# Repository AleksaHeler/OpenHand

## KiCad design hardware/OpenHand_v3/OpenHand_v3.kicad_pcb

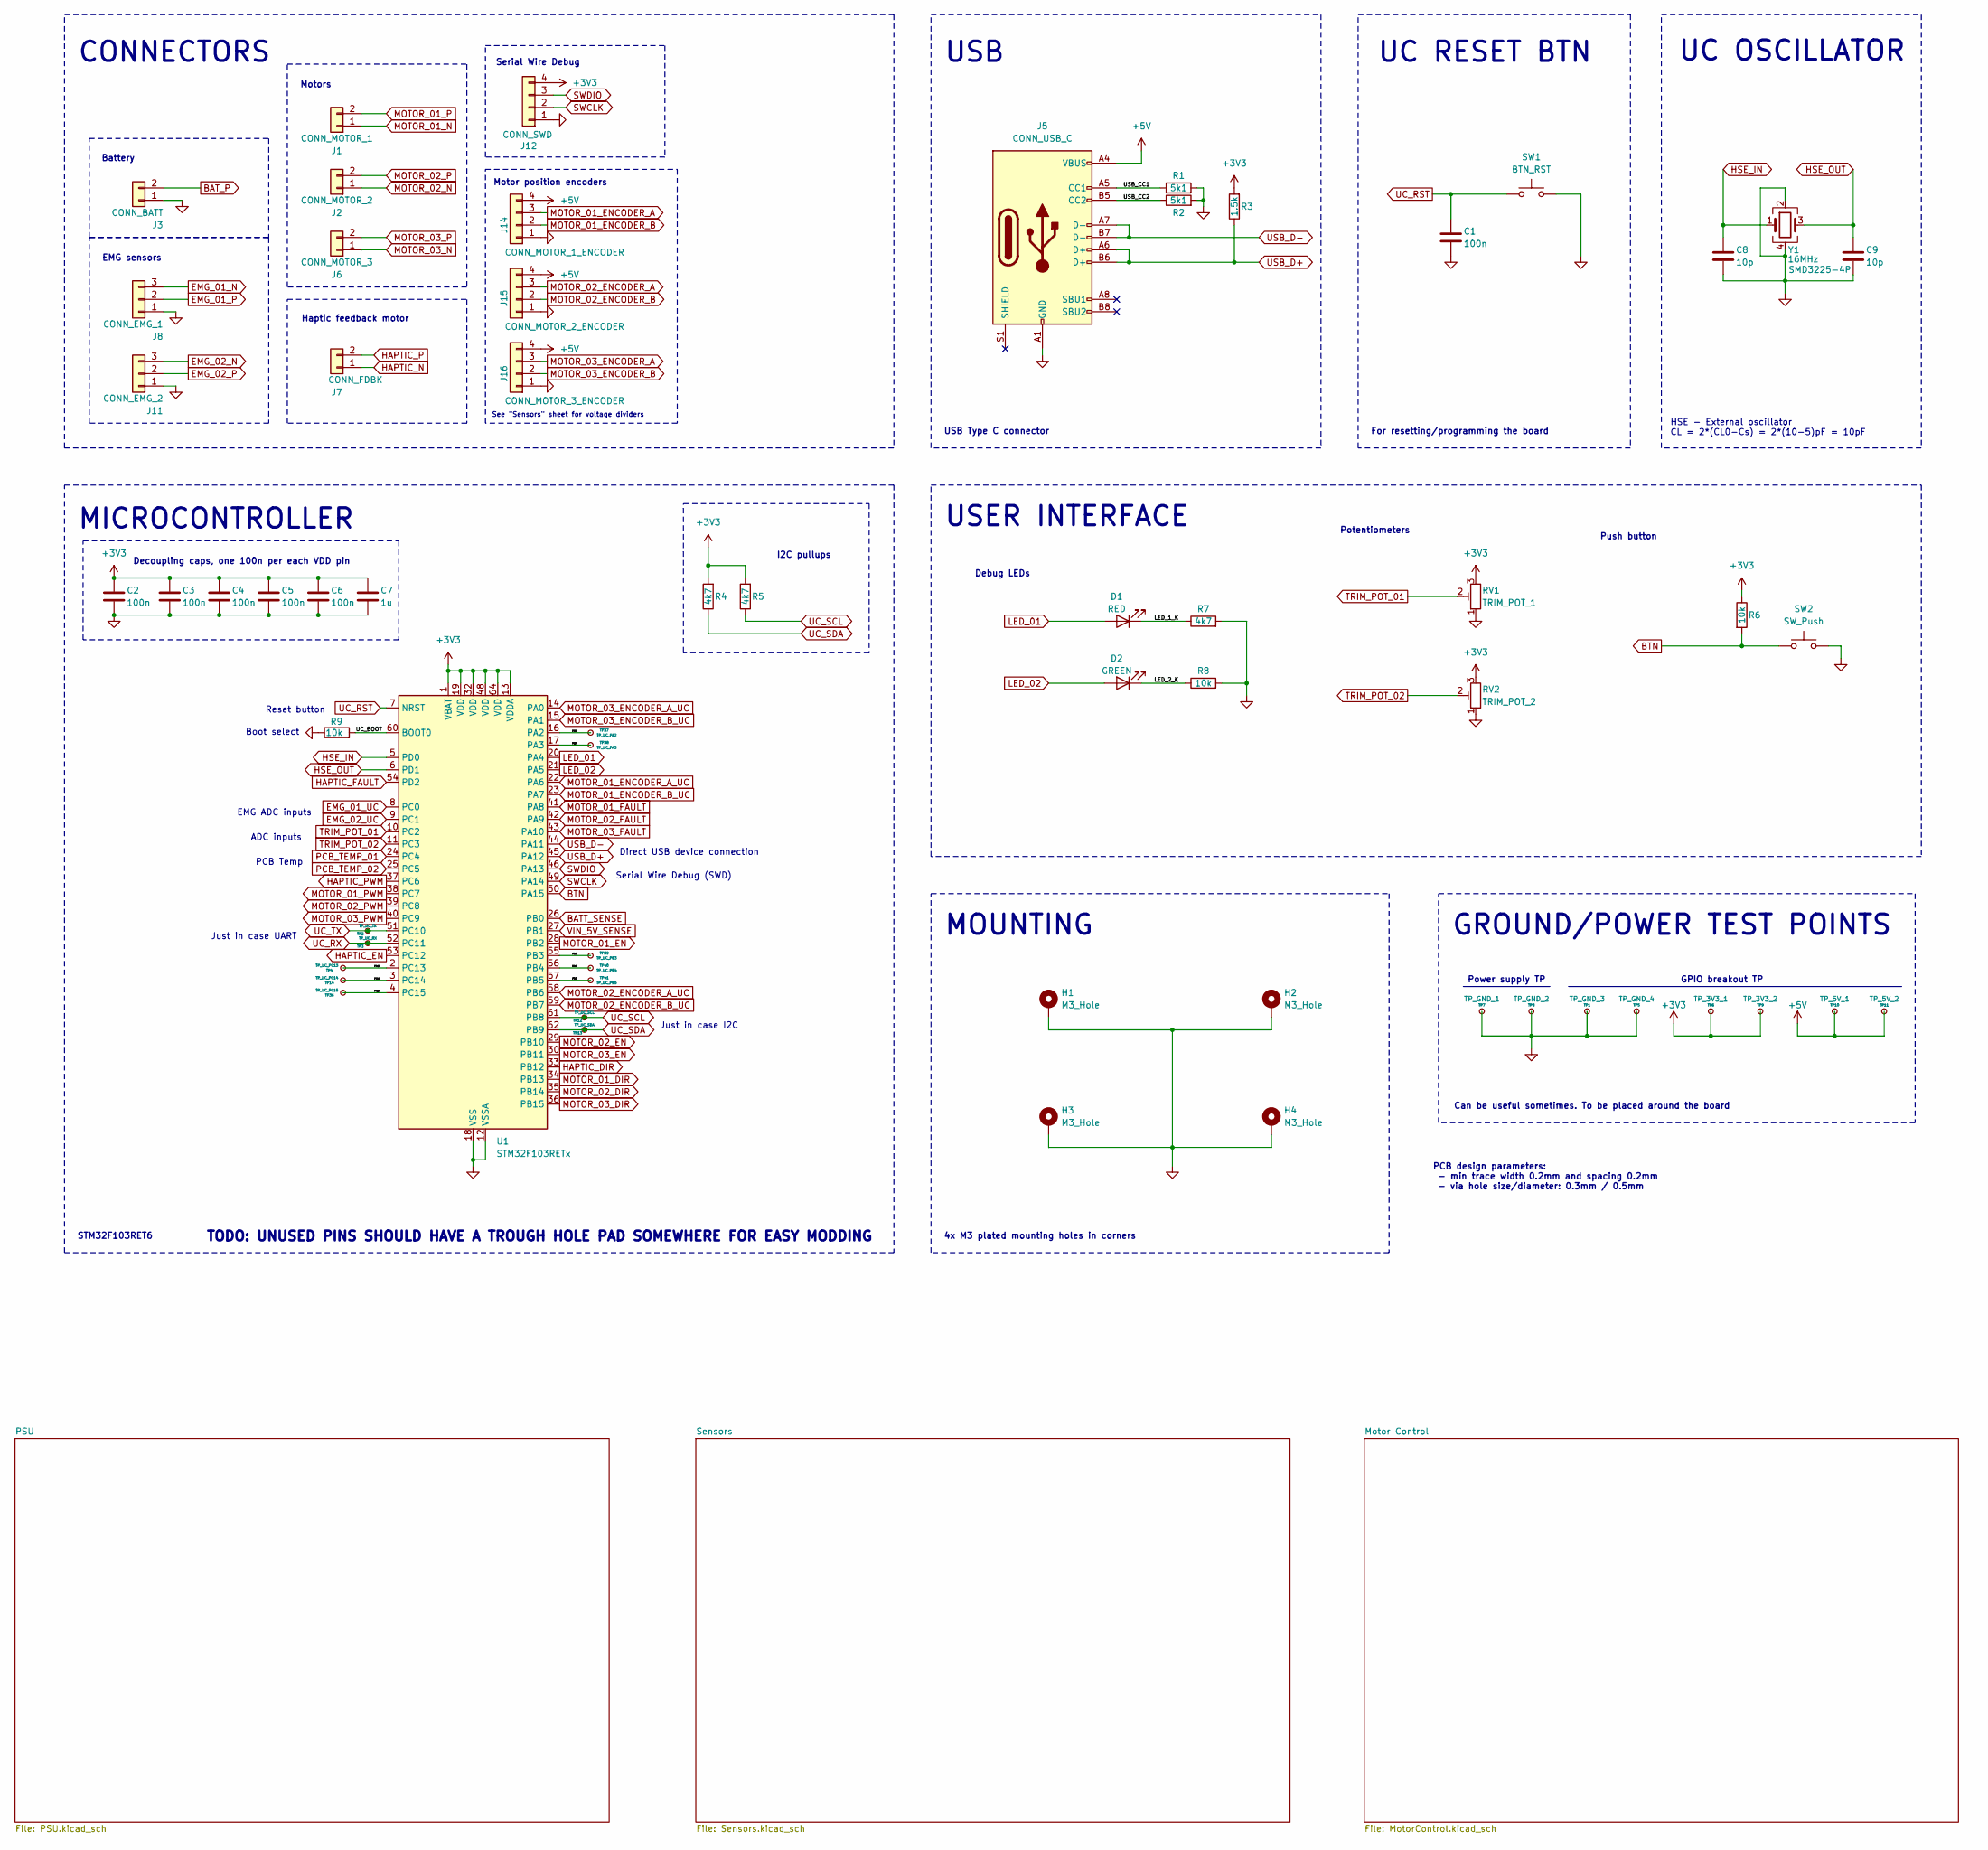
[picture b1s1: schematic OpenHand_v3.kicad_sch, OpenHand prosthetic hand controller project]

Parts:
C1, C2, C3, C4, C5, C6: 100n; C_0805_2012Metric
C7: 1u; C_0805_2012Metric
C8, C9: 10p; C_0805_2012Metric
D1: RED; LED_1210_3225Metric
D2: GREEN; LED_1210_3225Metric
H1, H2, H3, H4: M3_Hole; MountingHole_3.2mm_M3_Pad_Via
J1: CONN_MOTOR_1; JST_EH_S2B-EH_1x02_P2.50mm_Horizontal
J2: CONN_MOTOR_2; JST_EH_S2B-EH_1x02_P2.50mm_Horizontal
J3: CONN_BATT; JST_EH_S2B-EH_1x02_P2.50mm_Horizontal
J5: CONN_USB_C; USB_C_Receptacle_G-Switch_GT-USB-7010ASV
J6: CONN_MOTOR_3; JST_EH_S2B-EH_1x02_P2.50mm_Horizontal
J7: CONN_FDBK; JST_EH_S2B-EH_1x02_P2.50mm_Horizontal
J8: CONN_EMG_1; JST_XH_B3B-XH-A_1x03_P2.50mm_Vertical
J11: CONN_EMG_2; JST_XH_B3B-XH-A_1x03_P2.50mm_Vertical
J12: CONN_SWD; JST_XH_B4B-XH-A_1x04_P2.50mm_Vertical
J14: CONN_MOTOR_1_ENCODER; JST_XH_B4B-XH-A_1x04_P2.50mm_Vertical
J15: CONN_MOTOR_2_ENCODER; JST_XH_B4B-XH-A_1x04_P2.50mm_Vertical
J16: CONN_MOTOR_3_ENCODER; JST_XH_B4B-XH-A_1x04_P2.50mm_Vertical
R1, R2: 5k1; R_0805_2012Metric
R3: 1.5k; R_0805_2012Metric
R4, R5, R7: 4k7; R_0805_2012Metric
R6, R8, R9: 10k; R_0805_2012Metric
RV1: TRIM_POT_1; Potentiometer_Vishay_TS53YJ_Vertical
RV2: TRIM_POT_2; Potentiometer_Vishay_TS53YJ_Vertical
SW1: BTN_RST; SW_Tactile_SPST_NO_Straight_CK_PTS636Sx25SMTRLFS
SW2: SW_Push; SW_Tactile_SPST_NO_Straight_CK_PTS636Sx25SMTRLFS
TP1: TP_GND_3; TestPoint_THTPad_D1.5mm_Drill0.7mm
TP2: TP_UC_TX; TestPoint_THTPad_D1.5mm_Drill0.7mm
TP3: TP_UC_RX; TestPoint_THTPad_D1.5mm_Drill0.7mm
TP4: TP_UC_PC13; TestPoint_THTPad_D1.5mm_Drill0.7mm
TP5: TP_GND_4; TestPoint_THTPad_D1.5mm_Drill0.7mm
TP6: TP_3V3_1; TestPoint_THTPad_D1.5mm_Drill0.7mm
TP7: TP_GND_1; TestPoint_THTPad_D1.5mm_Drill0.7mm
TP8: TP_GND_2; TestPoint_THTPad_D1.5mm_Drill0.7mm
TP9: TP_3V3_2; TestPoint_THTPad_D1.5mm_Drill0.7mm
TP10: TP_5V_1; TestPoint_THTPad_D1.5mm_Drill0.7mm
TP11: TP_5V_2; TestPoint_THTPad_D1.5mm_Drill0.7mm
TP12: TP_UC_SCL; TestPoint_THTPad_D1.5mm_Drill0.7mm
TP13: TP_UC_SDA; TestPoint_THTPad_D1.5mm_Drill0.7mm
TP14: TP_UC_PC14; TestPoint_THTPad_D1.5mm_Drill0.7mm
TP36: TP_UC_PC15; TestPoint_THTPad_D1.5mm_Drill0.7mm
TP37: TP_UC_PA2; TestPoint_THTPad_D1.5mm_Drill0.7mm
TP38: TP_UC_PA3; TestPoint_THTPad_D1.5mm_Drill0.7mm
TP39: TP_UC_PB3; TestPoint_THTPad_D1.5mm_Drill0.7mm
TP40: TP_UC_PB4; TestPoint_THTPad_D1.5mm_Drill0.7mm
TP41: TP_UC_PB5; TestPoint_THTPad_D1.5mm_Drill0.7mm
U1: STM32F103RETx; LQFP-64_10x10mm_P0.5mm
Y1: 16MHz; Crystal_SMD_3225-4Pin_3.2x2.5mm

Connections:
+3V3: C2.1, C3.1, C4.1, C5.1, C6.1, C7.1, J12.4, R3.2, R4.2, R5.2, R6.1, RV1.3, RV2.3, TP6.1, TP9.1, U1.1 (VBAT), U1.13 (VDDA), U1.19 (VDD), U1.32 (VDD), U1.48 (VDD), U1.64 (VDD); also elsewhere on the board
+5V: J5.A4 (VBUS), J5.A9 (VBUS), J5.B4 (VBUS), J5.B9 (VBUS), J14.4, J15.4, J16.4, TP10.1, TP11.1; also elsewhere on the board
/LED_1_K: D1.1 (K), R7.1
/LED_2_K: D2.1 (K), R8.1
/PA2: TP37.1, U1.16 (PA2)
/PA3: TP38.1, U1.17 (PA3)
/PB3: TP39.1, U1.55 (PB3)
/PB4: TP40.1, U1.56 (PB4)
/PB5: TP41.1, U1.57 (PB5)
/PC13: TP4.1, U1.2 (PC13)
/PC14: TP14.1, U1.3 (PC14)
/PC15: TP36.1, U1.4 (PC15)
/UC_BOOT: R9.2, U1.60 (BOOT0)
/USB_CC1: J5.A5 (CC1), R1.1
/USB_CC2: J5.B5 (CC2), R2.1
BATT_SENSE: U1.26 (PB0); also elsewhere on the board
BAT_P: J3.2; also elsewhere on the board
BTN: R6.2, SW2.1, U1.50 (PA15)
EMG_01_N: J8.3; also elsewhere on the board
EMG_01_P: J8.2; also elsewhere on the board
EMG_01_UC: U1.8 (PC0); also elsewhere on the board
EMG_02_N: J11.3; also elsewhere on the board
EMG_02_P: J11.2; also elsewhere on the board
EMG_02_UC: U1.9 (PC1); also elsewhere on the board
GND: C1.2, C2.2, C3.2, C4.2, C5.2, C6.2, C7.2, C8.2, C9.2, H1.1, H2.1, H3.1, H4.1, J3.1, J5.A1 (GND), J5.A12 (GND), J5.B1 (GND), J5.B12 (GND), J8.1, J11.1, J12.1, J14.1, J15.1, J16.1, R1.2, R2.2, R7.2, R8.2, R9.1, RV1.1, RV2.1, SW1.2, SW2.2, TP1.1, TP5.1, TP7.1, TP8.1, U1.12 (VSSA), U1.18 (VSS), U1.31 (VSS), U1.47 (VSS), U1.63 (VSS), Y1.2, Y1.4; also elsewhere on the board
HAPTIC_DIR: U1.33 (PB12); also elsewhere on the board
HAPTIC_EN: U1.53 (PC12); also elsewhere on the board
HAPTIC_FAULT: U1.54 (PD2); also elsewhere on the board
HAPTIC_N: J7.1; also elsewhere on the board
HAPTIC_P: J7.2; also elsewhere on the board
HAPTIC_PWM: U1.37 (PC6); also elsewhere on the board
HSE_IN: C8.1, U1.5 (PD0), Y1.1
HSE_OUT: C9.1, U1.6 (PD1), Y1.3
LED_01: D1.2 (A), U1.20 (PA4)
LED_02: D2.2 (A), U1.21 (PA5)
MOTOR_01_DIR: U1.34 (PB13); also elsewhere on the board
MOTOR_01_EN: U1.28 (PB2); also elsewhere on the board
MOTOR_01_ENCODER_A: J14.3; also elsewhere on the board
MOTOR_01_ENCODER_A_UC: U1.22 (PA6); also elsewhere on the board
MOTOR_01_ENCODER_B: J14.2; also elsewhere on the board
MOTOR_01_ENCODER_B_UC: U1.23 (PA7); also elsewhere on the board
MOTOR_01_FAULT: U1.41 (PA8); also elsewhere on the board
MOTOR_01_N: J1.1; also elsewhere on the board
MOTOR_01_P: J1.2; also elsewhere on the board
MOTOR_01_PWM: U1.38 (PC7); also elsewhere on the board
MOTOR_02_DIR: U1.35 (PB14); also elsewhere on the board
MOTOR_02_EN: U1.29 (PB10); also elsewhere on the board
MOTOR_02_ENCODER_A: J15.3; also elsewhere on the board
MOTOR_02_ENCODER_A_UC: U1.58 (PB6); also elsewhere on the board
MOTOR_02_ENCODER_B: J15.2; also elsewhere on the board
MOTOR_02_ENCODER_B_UC: U1.59 (PB7); also elsewhere on the board
MOTOR_02_FAULT: U1.42 (PA9); also elsewhere on the board
MOTOR_02_N: J2.1; also elsewhere on the board
MOTOR_02_P: J2.2; also elsewhere on the board
MOTOR_02_PWM: U1.39 (PC8); also elsewhere on the board
MOTOR_03_DIR: U1.36 (PB15); also elsewhere on the board
MOTOR_03_EN: U1.30 (PB11); also elsewhere on the board
MOTOR_03_ENCODER_A: J16.3; also elsewhere on the board
MOTOR_03_ENCODER_A_UC: U1.14 (PA0); also elsewhere on the board
MOTOR_03_ENCODER_B: J16.2; also elsewhere on the board
MOTOR_03_ENCODER_B_UC: U1.15 (PA1); also elsewhere on the board
MOTOR_03_FAULT: U1.43 (PA10); also elsewhere on the board
MOTOR_03_N: J6.1; also elsewhere on the board
MOTOR_03_P: J6.2; also elsewhere on the board
MOTOR_03_PWM: U1.40 (PC9); also elsewhere on the board
PCB_TEMP_01: U1.24 (PC4); also elsewhere on the board
PCB_TEMP_02: U1.25 (PC5); also elsewhere on the board
SWCLK: J12.2, U1.49 (PA14)
SWDIO: J12.3, U1.46 (PA13)
TRIM_POT_01: RV1.2, U1.10 (PC2)
TRIM_POT_02: RV2.2, U1.11 (PC3)
UC_RST: C1.1, SW1.1, U1.7 (NRST)
UC_RX: TP3.1, U1.52 (PC11)
UC_SCL: R5.1, TP12.1, U1.61 (PB8)
UC_SDA: R4.1, TP13.1, U1.62 (PB9)
UC_TX: TP2.1, U1.51 (PC10)
USB_D+: J5.A6 (D+), J5.B6 (D+), R3.1, U1.45 (PA12)
USB_D-: J5.A7 (D-), J5.B7 (D-), U1.44 (PA11)
VIN_5V_SENSE: U1.27 (PB1); also elsewhere on the board

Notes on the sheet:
I2C pullups
Debug LEDs
UC RESET BTN
Potentiometers
ADC inputs
Serial Wire Debug (SWD)
MICROCONTROLLER
Battery
PCB Temp
Haptic feedback motor
Reset button
Just in case I2C
USB
Push button
4x M3 plated mounting holes in corners
TODO: UNUSED PINS SHOULD HAVE A TROUGH HOLE PAD SOMEWHERE FOR EASY MODDING
Power supply TP
Motors
MOUNTING
CONNECTORS
PCB design parameters: - min trace width 0.2mm and spacing 0.2mm - via hole size/diameter: 0.3mm / 0.5mm
EMG ADC inputs
For resetting/programming the board
Can be useful sometimes. To be placed around the board
USB Type C connector
Decoupling caps, one 100n per each VDD pin
USER INTERFACE
STM32F103RET6
GROUND/POWER TEST POINTS
Boot select
GPIO breakout TP
EMG sensors
Direct USB device connection
HSE - External oscillator CL = 2*(CL0-Cs) = 2*(10-5)pF = 10pF
See "Sensors" sheet for voltage dividers
UC OSCILLATOR
Just in case UART
Serial Wire Debug
Motor position encoders

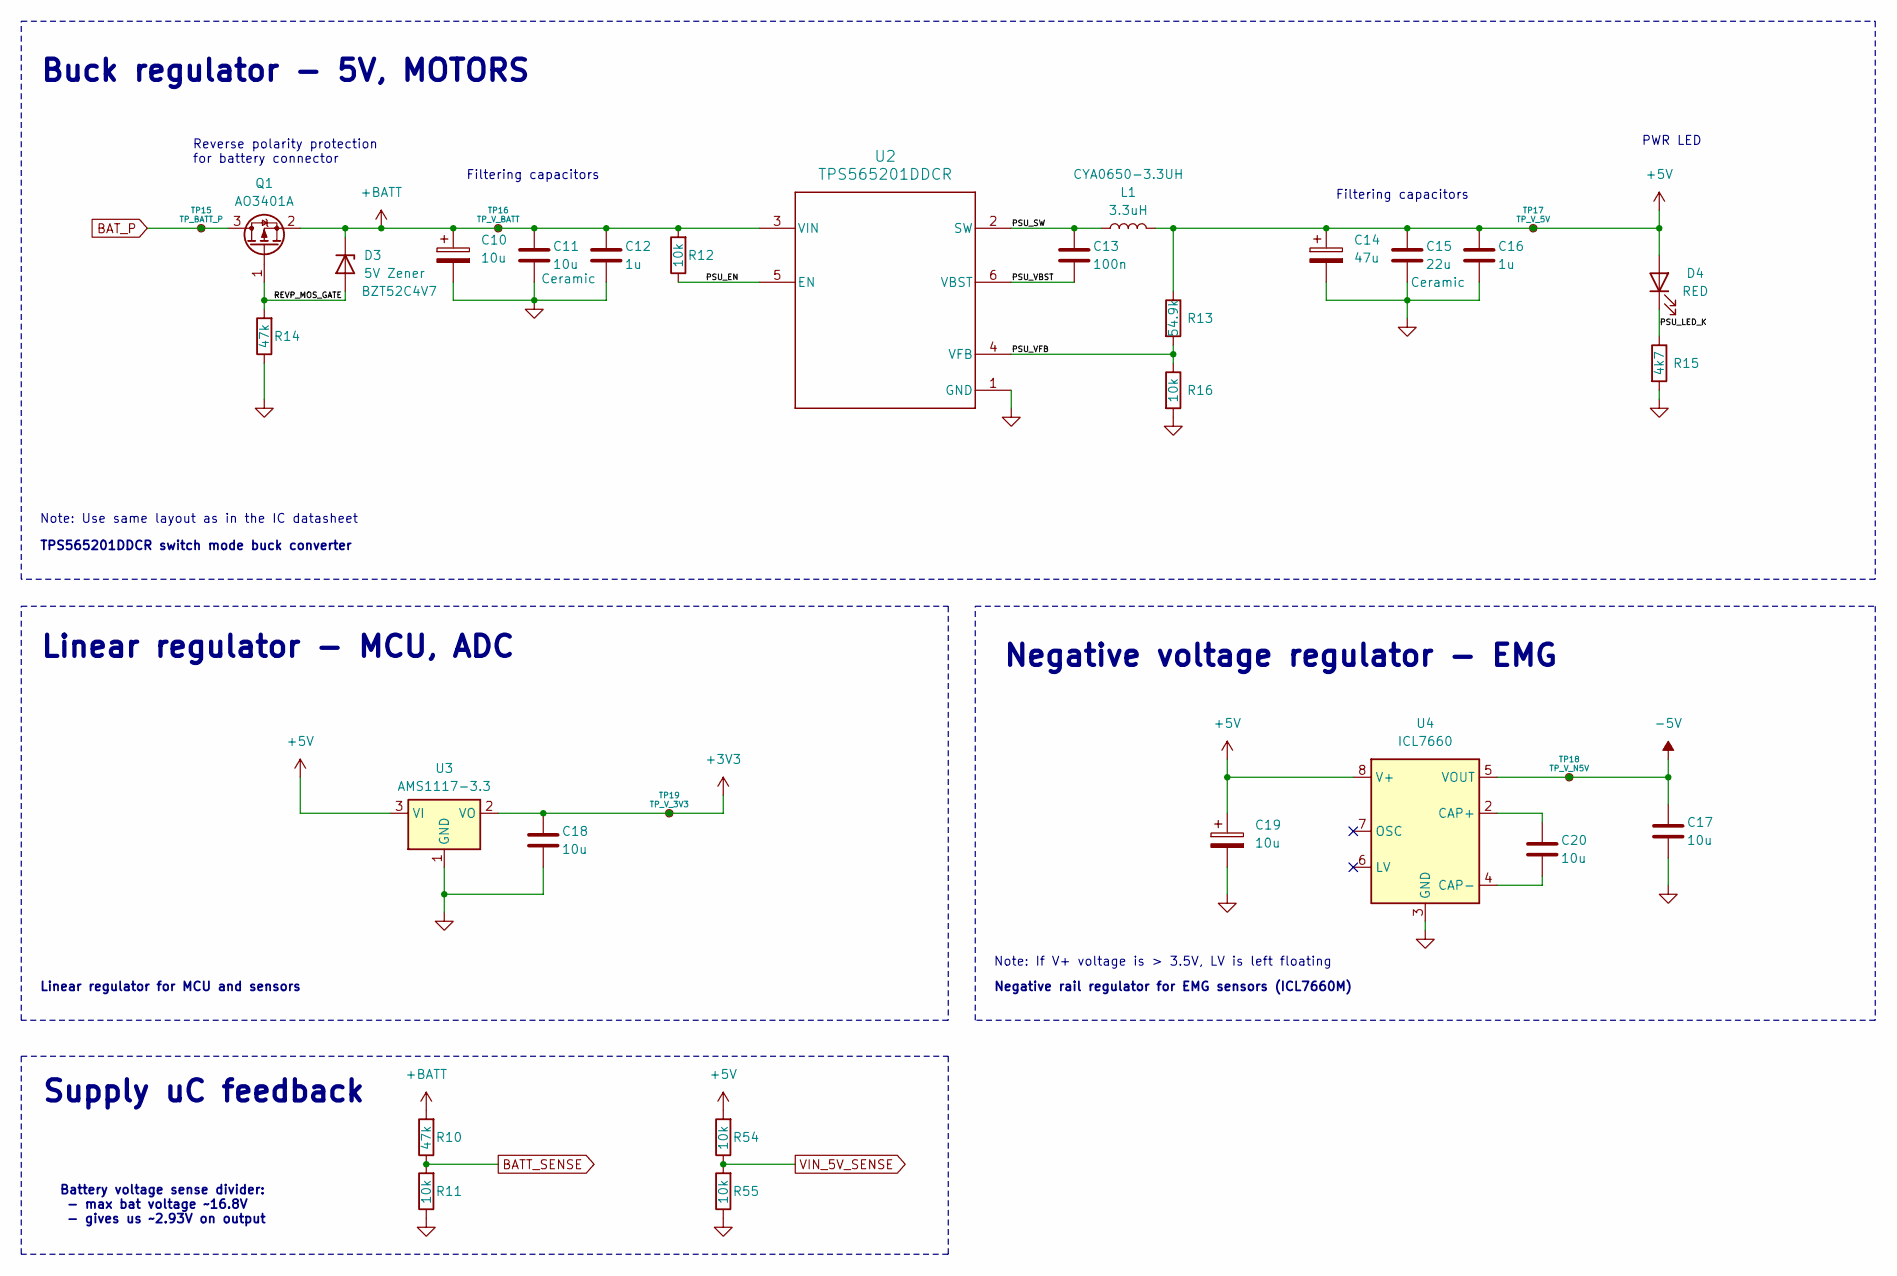
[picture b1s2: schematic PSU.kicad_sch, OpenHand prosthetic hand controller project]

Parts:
C10, C19: 10u; CP_Elec_4x5.4
C11, C17, C18, C20: 10u; C_0805_2012Metric
C12, C16: 1u; C_0805_2012Metric
C13: 100n; C_0805_2012Metric
C14: 47u; CP_Elec_6.3x5.4
C15: 22u; C_0805_2012Metric
D3: 5V Zener; D_SOD-123; Part Number BZT52C4V7
D4: RED; LED_1210_3225Metric
L1: 3.3uH; L_Bourns_SRP7028A_7.3x6.6mm; Part Number CYA0650-3.3UH
Q1: AO3401A; SOT-23
R10, R14: 47k; R_0805_2012Metric
R11, R12, R16, R54, R55: 10k; R_0805_2012Metric
R13: 54.9k; R_0805_2012Metric
R15: 4k7; R_0805_2012Metric
TP15: TP_BATT_P; TestPoint_Pad_D1.0mm
TP16: TP_V_BATT; TestPoint_Pad_D1.0mm
TP17: TP_V_5V; TestPoint_THTPad_D1.5mm_Drill0.7mm
TP18: TP_V_N5V; TestPoint_THTPad_D1.5mm_Drill0.7mm
TP19: TP_V_3V3; TestPoint_THTPad_D1.5mm_Drill0.7mm
U2: TPS565201DDCR; TPS565201DDCR_L
U3: AMS1117-3.3; SOT-223-3_TabPin2
U4: ICL7660; SOP-8_3.9x4.9mm_P1.27mm

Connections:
+3V3: C18.1, TP19.1, U3.2 (VO); also elsewhere on the board
+5V: C14.1, C15.1, C16.1, C19.1, D4.2 (A), L1.2, R13.1, R54.2, TP17.1, U3.3 (VI), U4.8 (V+); also elsewhere on the board
+BATT: C10.1, C11.1, C12.1, D3.1 (K), Q1.2 (S), R10.2, R12.2, TP16.1, U2.3 (VIN)
-5V: C17.1, TP18.1, U4.5 (VOUT); also elsewhere on the board
/PSU/PSU_EN: R12.1, U2.5 (EN)
/PSU/PSU_LED_K: D4.1 (K), R15.1
/PSU/PSU_SW: C13.1, L1.1, U2.2 (SW)
/PSU/PSU_VBST: C13.2, U2.6 (VBST)
/PSU/PSU_VFB: R13.2, R16.1, U2.4 (VFB)
/PSU/REVP_MOS_GATE: D3.2 (A), Q1.1 (G), R14.2
BATT_SENSE: R10.1, R11.2; also elsewhere on the board
BAT_P: Q1.3 (D), TP15.1; also elsewhere on the board
GND: C10.2, C11.2, C12.2, C14.2, C15.2, C16.2, C17.2, C18.2, C19.2, R11.1, R14.1, R15.2, R16.2, R55.1, U2.1 (GND), U3.1 (GND), U4.3 (GND); also elsewhere on the board
unnamed: C20.1, U4.2 (CAP+)
unnamed: C20.2, U4.4 (CAP-)
VIN_5V_SENSE: R54.1, R55.2; also elsewhere on the board

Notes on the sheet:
Linear regulator - MCU, ADC
Note: Use same layout as in the IC datasheet
Filtering capacitors
Supply uC feedback
PWR LED
Note: If V+ voltage is > 3.5V, LV is left floating
Negative voltage regulator - EMG
Buck regulator - 5V, MOTORS
TPS565201DDCR switch mode buck converter
Battery voltage sense divider: - max bat voltage ~16.8V - gives us ~2.93V on output
Negative rail regulator for EMG sensors (ICL7660M)
Linear regulator for MCU and sensors
Reverse polarity protection for battery connector

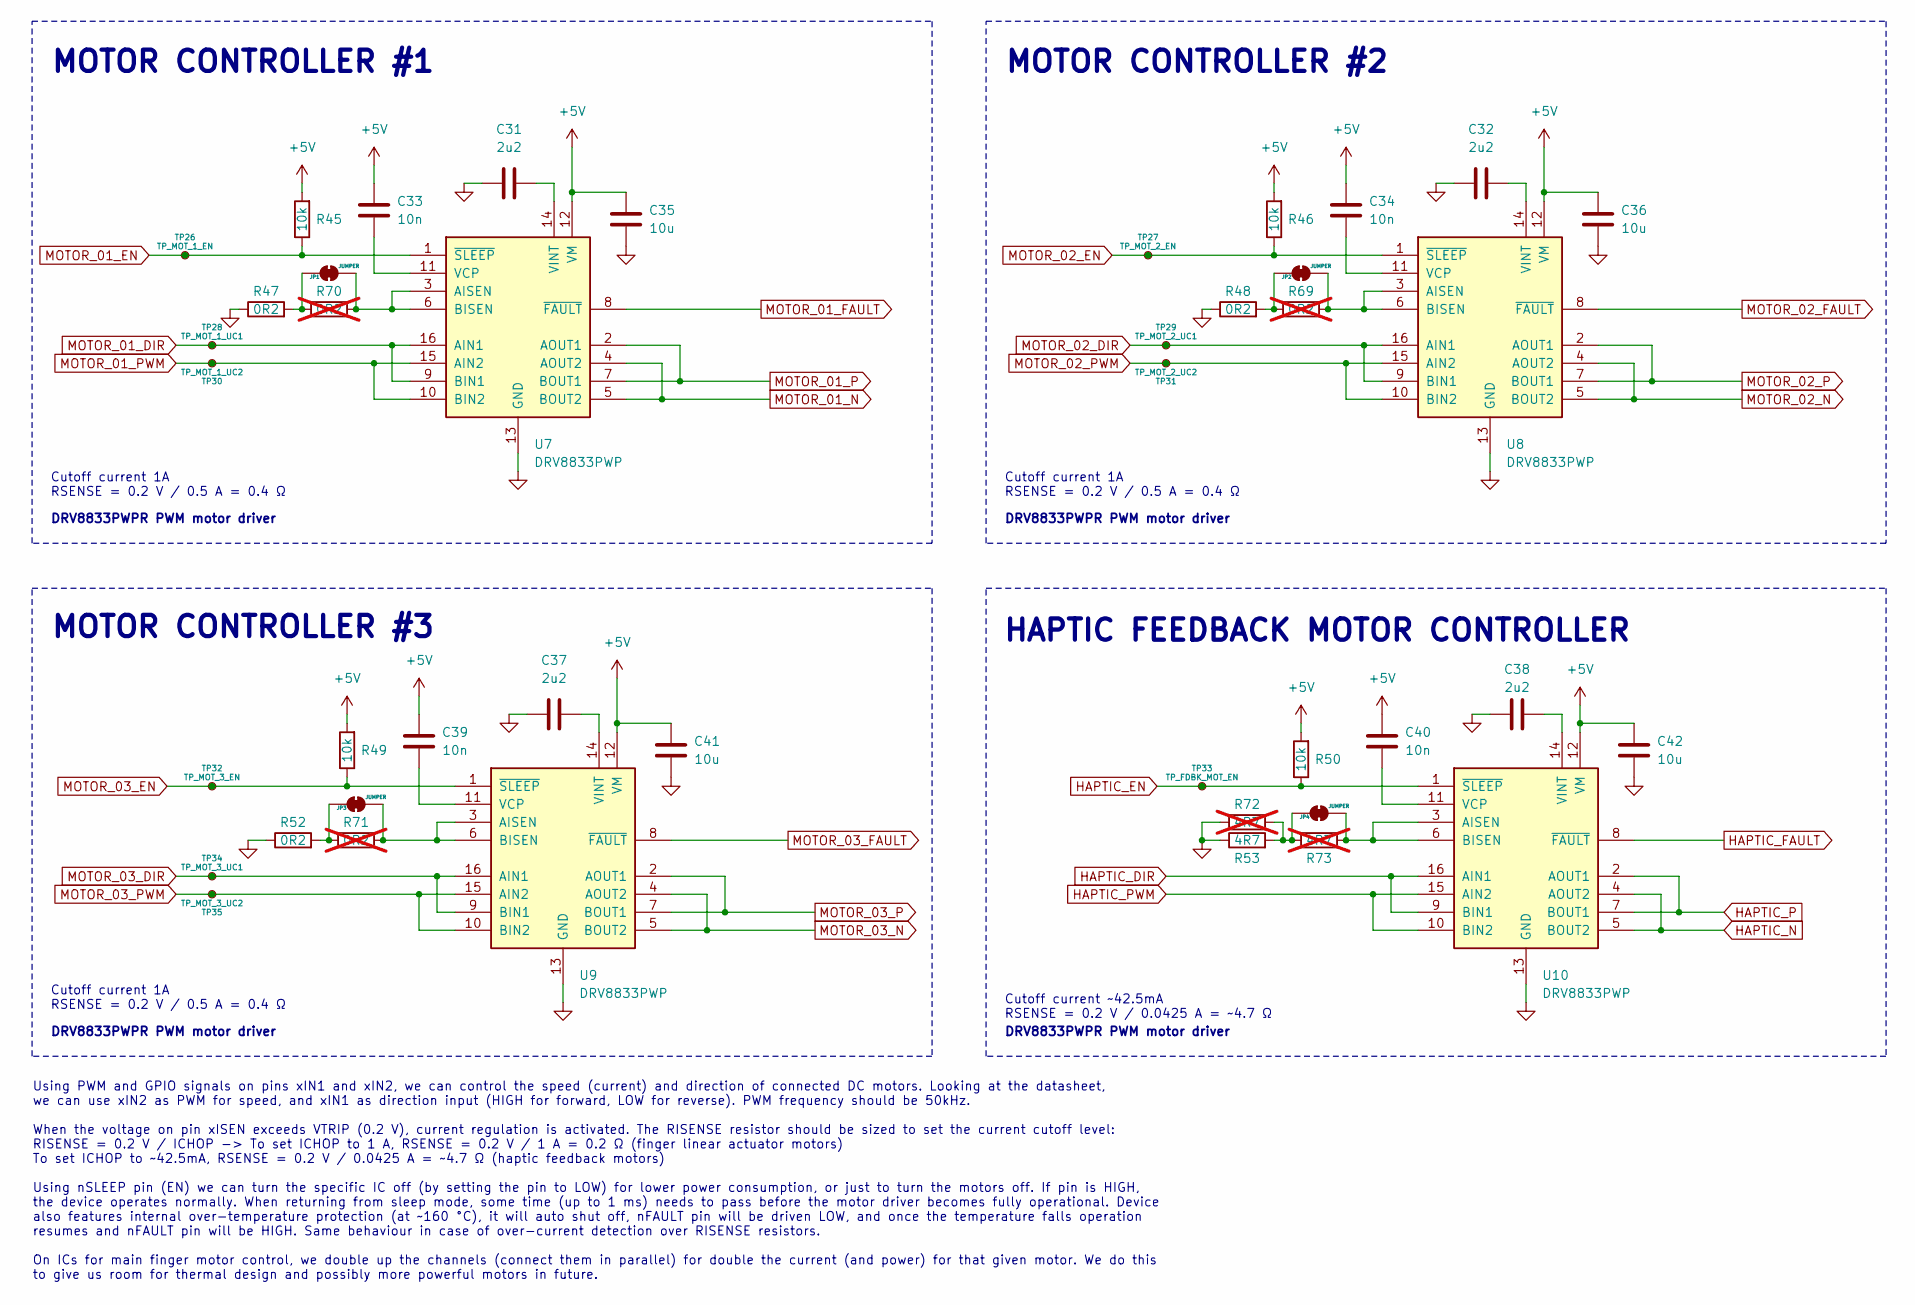
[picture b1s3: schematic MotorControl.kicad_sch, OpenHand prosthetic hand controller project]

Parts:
C31, C32, C37, C38: 2u2; C_0805_2012Metric
C33, C34, C39, C40: 10n; C_0805_2012Metric
C35, C36, C41, C42: 10u; C_0805_2012Metric
JP1, JP2, JP3, JP4: JUMPER; SolderJumper-2_P1.3mm_Bridged_RoundedPad1.0x1.5mm
R45, R46, R49, R50: 10k; R_0805_2012Metric
R47, R48, R52: 0R2; R_1206_3216Metric
R53: 4R7; R_1206_3216Metric
R69, R70, R71: 0R2; R_1206_3216Metric; not fitted
R72, R73: 4R7; R_1206_3216Metric; not fitted
TP26: TP_MOT_1_EN; TestPoint_Pad_D1.0mm
TP27: TP_MOT_2_EN; TestPoint_Pad_D1.0mm
TP28: TP_MOT_1_UC1; TestPoint_Pad_D1.0mm
TP29: TP_MOT_2_UC1; TestPoint_Pad_D1.0mm
TP30: TP_MOT_1_UC2; TestPoint_Pad_D1.0mm
TP31: TP_MOT_2_UC2; TestPoint_Pad_D1.0mm
TP32: TP_MOT_3_EN; TestPoint_Pad_D1.0mm
TP33: TP_FDBK_MOT_EN; TestPoint_Pad_D1.0mm
TP34: TP_MOT_3_UC1; TestPoint_Pad_D1.0mm
TP35: TP_MOT_3_UC2; TestPoint_Pad_D1.0mm
U7, U8, U9, U10: DRV8833PWP; HTSSOP-16-1EP_4.4x5mm_P0.65mm_EP3.4x5mm_Mask2.46x2.31mm_The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

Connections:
+5V: C33.1, C34.1, C35.1, C36.1, C39.1, C40.1, C41.1, C42.1, R45.2, R46.2, R49.2, R50.2, U7.12 (VM), U8.12 (VM), U9.12 (VM), U10.12 (VM); also elsewhere on the board
GND: C31.1, C32.1, C35.2, C36.2, C37.1, C38.1, C41.2, C42.2, R47.1, R48.1, R52.1, R53.1, R72.2, U7.13 (GND), U7.17 (GND), U8.13 (GND), U8.17 (GND), U9.13 (GND), U9.17 (GND), U10.13 (GND), U10.17 (GND); also elsewhere on the board
HAPTIC_DIR: U10.9 (BIN1), U10.16 (AIN1); also elsewhere on the board
HAPTIC_EN: R50.1, TP33.1, U10.1 (~SLEEP); also elsewhere on the board
HAPTIC_FAULT: U10.8 (~FAULT); also elsewhere on the board
HAPTIC_N: U10.4 (AOUT2), U10.5 (BOUT2); also elsewhere on the board
HAPTIC_P: U10.2 (AOUT1), U10.7 (BOUT1); also elsewhere on the board
HAPTIC_PWM: U10.10 (BIN2), U10.15 (AIN2); also elsewhere on the board
MOTOR_01_DIR: TP28.1, U7.9 (BIN1), U7.16 (AIN1); also elsewhere on the board
MOTOR_01_EN: R45.1, TP26.1, U7.1 (~SLEEP); also elsewhere on the board
MOTOR_01_FAULT: U7.8 (~FAULT); also elsewhere on the board
MOTOR_01_N: U7.4 (AOUT2), U7.5 (BOUT2); also elsewhere on the board
MOTOR_01_P: U7.2 (AOUT1), U7.7 (BOUT1); also elsewhere on the board
MOTOR_01_PWM: TP30.1, U7.10 (BIN2), U7.15 (AIN2); also elsewhere on the board
MOTOR_02_DIR: TP29.1, U8.9 (BIN1), U8.16 (AIN1); also elsewhere on the board
MOTOR_02_EN: R46.1, TP27.1, U8.1 (~SLEEP); also elsewhere on the board
MOTOR_02_FAULT: U8.8 (~FAULT); also elsewhere on the board
MOTOR_02_N: U8.4 (AOUT2), U8.5 (BOUT2); also elsewhere on the board
MOTOR_02_P: U8.2 (AOUT1), U8.7 (BOUT1); also elsewhere on the board
MOTOR_02_PWM: TP31.1, U8.10 (BIN2), U8.15 (AIN2); also elsewhere on the board
MOTOR_03_DIR: TP34.1, U9.9 (BIN1), U9.16 (AIN1); also elsewhere on the board
MOTOR_03_EN: R49.1, TP32.1, U9.1 (~SLEEP); also elsewhere on the board
MOTOR_03_FAULT: U9.8 (~FAULT); also elsewhere on the board
MOTOR_03_N: U9.4 (AOUT2), U9.5 (BOUT2); also elsewhere on the board
MOTOR_03_P: U9.2 (AOUT1), U9.7 (BOUT1); also elsewhere on the board
MOTOR_03_PWM: TP35.1, U9.10 (BIN2), U9.15 (AIN2); also elsewhere on the board
unnamed: JP1.1 (A), R47.2, R70.1
unnamed: JP1.2 (B), R70.2, U7.3 (AISEN), U7.6 (BISEN)
unnamed: JP2.1 (A), R48.2, R69.1
unnamed: JP2.2 (B), R69.2, U8.3 (AISEN), U8.6 (BISEN)
unnamed: JP3.1 (A), R52.2, R71.1
unnamed: JP3.2 (B), R71.2, U9.3 (AISEN), U9.6 (BISEN)
unnamed: JP4.1 (A), R53.2, R72.1, R73.1
unnamed: JP4.2 (B), R73.2, U10.3 (AISEN), U10.6 (BISEN)
unnamed: C33.2, U7.11 (VCP)
unnamed: C31.2, U7.14 (VINT)
unnamed: C34.2, U8.11 (VCP)
unnamed: C32.2, U8.14 (VINT)
unnamed: C39.2, U9.11 (VCP)
unnamed: C37.2, U9.14 (VINT)
unnamed: C40.2, U10.11 (VCP)
unnamed: C38.2, U10.14 (VINT)

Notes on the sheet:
Cutoff current 1A RSENSE = 0.2 V / 0.5 A = 0.4 Ω
MOTOR CONTROLLER #1
DRV8833PWPR PWM motor driver
HAPTIC FEEDBACK MOTOR CONTROLLER
Using PWM and GPIO signals on pins xIN1 and xIN2, we can control the speed (current) and direction of connected DC motors. Looking at the datasheet, we can use xIN2 as PWM for speed, and xIN1 as direction input (HIGH for forward, LOW for reverse). PWM frequency should be 50kHz. When the voltage on 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
MOTOR CONTROLLER #3
MOTOR CONTROLLER #2
Cutoff current ~42.5mA RSENSE = 0.2 V / 0.0425 A = ~4.7 Ω
Cutoff current 1A RSENSE = 0.2 V / 0.5 A = 0.4 Ω

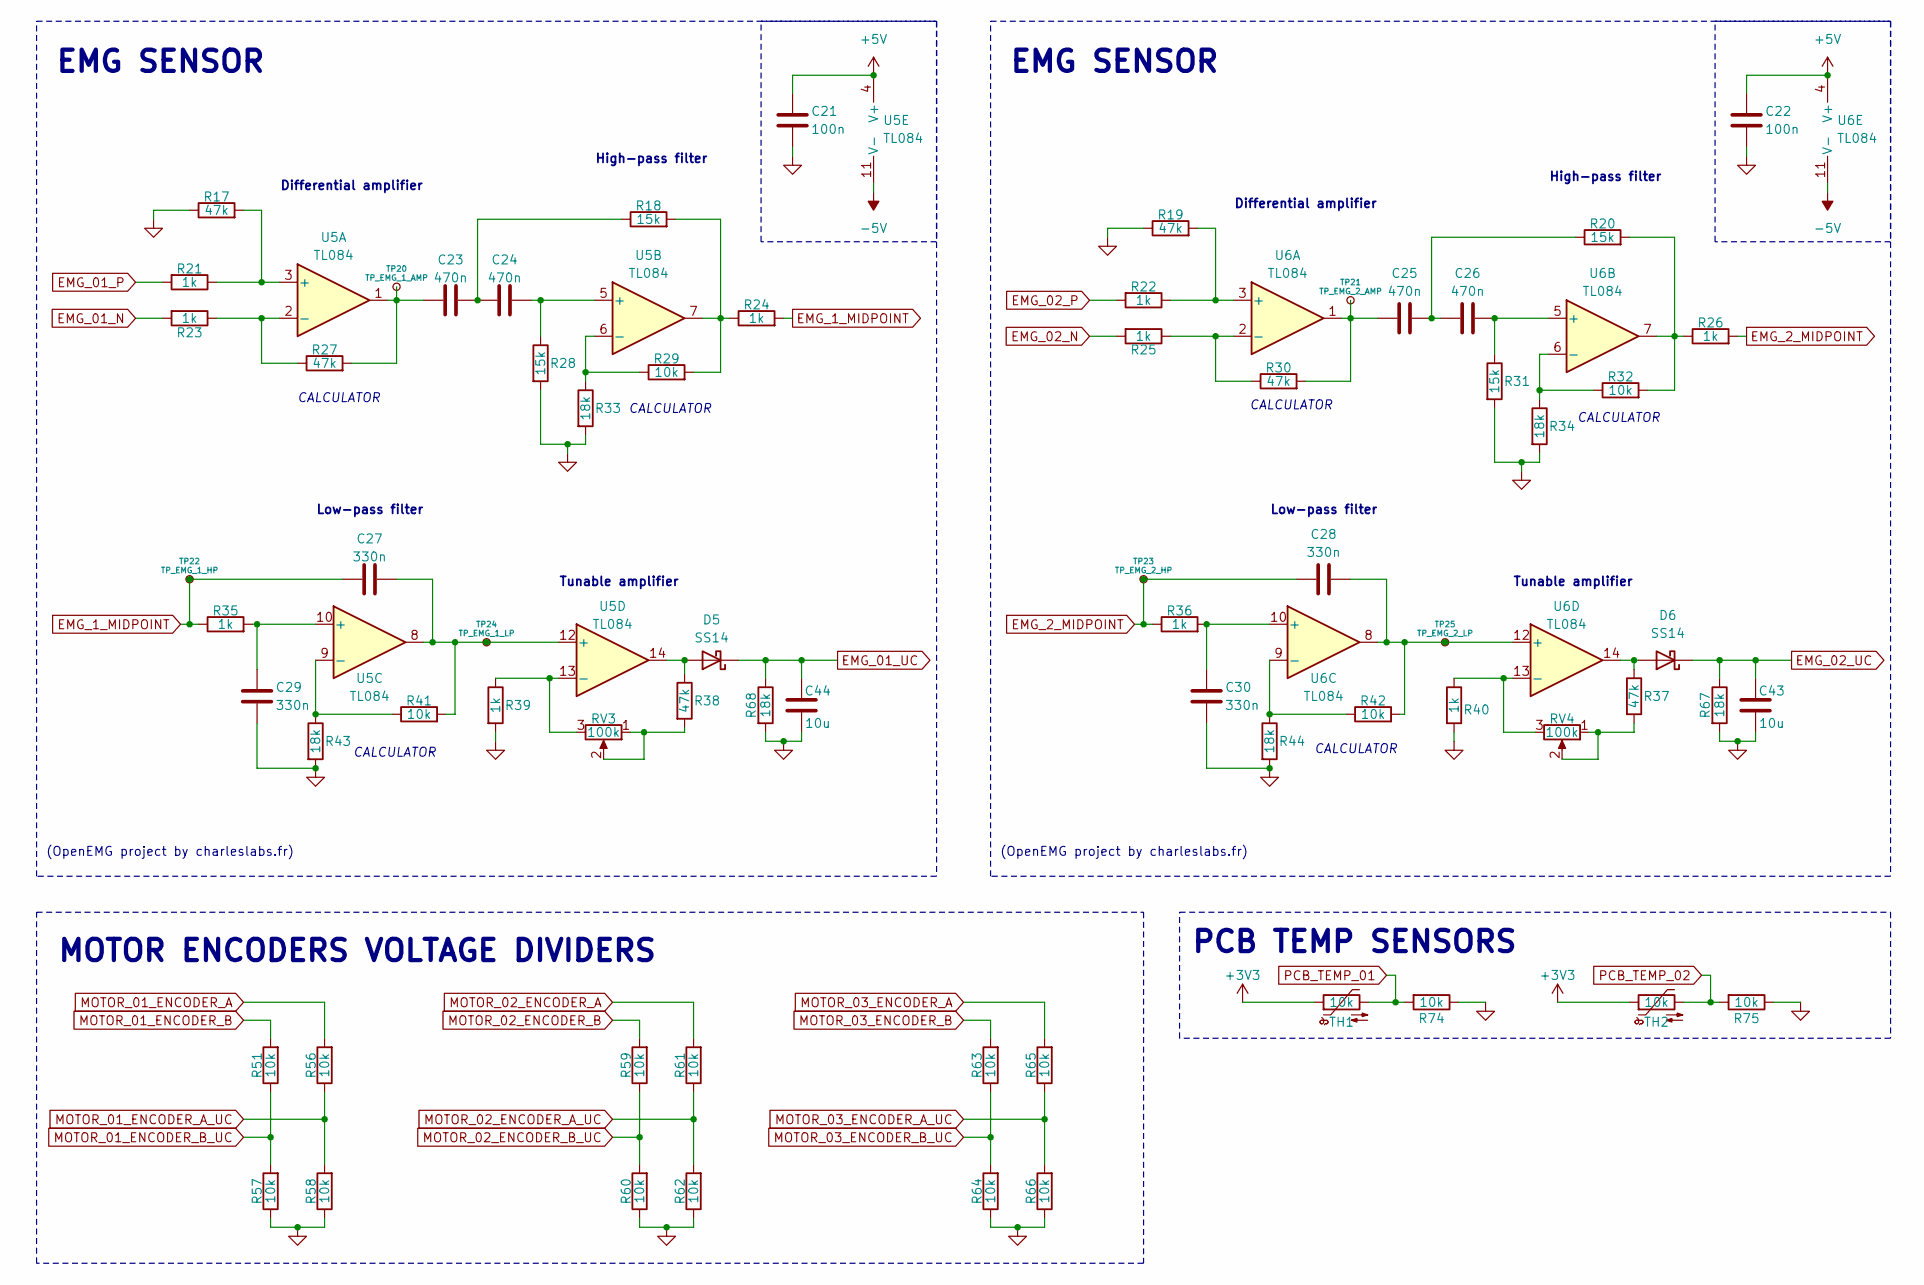
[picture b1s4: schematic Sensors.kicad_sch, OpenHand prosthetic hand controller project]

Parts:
C21, C22: 100n; C_0805_2012Metric
C23, C24, C25, C26: 470n; C_0805_2012Metric
C27, C28, C29, C30: 330n; C_0805_2012Metric
C43, C44: 10u; C_0805_2012Metric
D5, D6: SS14; D_SOD-123
R17, R19, R27, R30, R37, R38: 47k; R_0805_2012Metric
R18, R20, R28, R31: 15k; R_0805_2012Metric
R21, R22, R23, R24, R25, R26, R35, R36, R39, R40: 1k; R_0805_2012Metric
R29, R32, R41, R42, R51, R56, R57, R58, R59, R60, R61, R62, R63, R64, R65, R66, R74, R75: 10k; R_0805_2012Metric
R33, R34, R43, R44, R67, R68: 18k; R_0805_2012Metric
RV3, RV4: 100k; Potentiometer_Vishay_TS53YJ_Vertical
TH1, TH2: 10k; R_0805_2012Metric
TP20: TP_EMG_1_AMP; TestPoint_Pad_D1.0mm
TP21: TP_EMG_2_AMP; TestPoint_Pad_D1.0mm
TP22: TP_EMG_1_HP; TestPoint_Pad_D1.0mm
TP23: TP_EMG_2_HP; TestPoint_Pad_D1.0mm
TP24: TP_EMG_1_LP; TestPoint_Pad_D1.0mm
TP25: TP_EMG_2_LP; TestPoint_Pad_D1.0mm
U5, U6: TL084; SO-14_5.3x10.2mm_P1.27mm

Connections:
+3V3: TH1.1, TH2.1; also elsewhere on the board
+5V: C21.1, C22.1, U5.4 (V+), U6.4 (V+); also elsewhere on the board
-5V: U5.11 (V-), U6.11 (V-); also elsewhere on the board
EMG_1_MIDPOINT: C27.1, R24.2, R35.1, TP22.1
EMG_01_N: R23.2; also elsewhere on the board
EMG_01_P: R21.2; also elsewhere on the board
EMG_01_UC: C44.1, D5.1 (K), R68.1; also elsewhere on the board
EMG_2_MIDPOINT: C28.1, R26.2, R36.1, TP23.1
EMG_02_N: R25.2; also elsewhere on the board
EMG_02_P: R22.2; also elsewhere on the board
EMG_02_UC: C43.1, D6.1 (K), R67.1; also elsewhere on the board
GND: C21.2, C22.2, C29.1, C30.1, C43.2, C44.2, R17.1, R19.1, R28.2, R31.2, R33.2, R34.2, R39.2, R40.2, R43.2, R44.2, R57.1, R58.1, R60.1, R62.1, R64.1, R66.1, R67.2, R68.2, R74.1, R75.1; also elsewhere on the board
MOTOR_01_ENCODER_A: R56.2; also elsewhere on the board
MOTOR_01_ENCODER_A_UC: R56.1, R58.2; also elsewhere on the board
MOTOR_01_ENCODER_B: R51.2; also elsewhere on the board
MOTOR_01_ENCODER_B_UC: R51.1, R57.2; also elsewhere on the board
MOTOR_02_ENCODER_A: R61.2; also elsewhere on the board
MOTOR_02_ENCODER_A_UC: R61.1, R62.2; also elsewhere on the board
MOTOR_02_ENCODER_B: R59.2; also elsewhere on the board
MOTOR_02_ENCODER_B_UC: R59.1, R60.2; also elsewhere on the board
MOTOR_03_ENCODER_A: R65.2; also elsewhere on the board
MOTOR_03_ENCODER_A_UC: R65.1, R66.2; also elsewhere on the board
MOTOR_03_ENCODER_B: R63.2; also elsewhere on the board
MOTOR_03_ENCODER_B_UC: R63.1, R64.2; also elsewhere on the board
unnamed: C23.1, R27.2, TP20.1, U5.1
unnamed: C23.2, C24.1, R18.1
unnamed: C25.1, R30.2, TP21.1, U6.1
unnamed: C25.2, C26.1, R20.1
unnamed: D5.2 (A), R38.1, U5.14
unnamed: D6.2 (A), R37.1, U6.14
unnamed: R18.2, R24.1, R29.2, U5.7
unnamed: R20.2, R26.1, R32.2, U6.7
unnamed: R37.2, RV4.1, RV4.2
unnamed: R38.2, RV3.1, RV3.2
unnamed: R17.2, R21.1, U5.3 (+)
unnamed: R23.1, R27.1, U5.2 (-)
unnamed: C24.2, R28.1, U5.5 (+)
unnamed: R29.1, R33.1, U5.6 (-)
unnamed: C29.2, R35.2, U5.10 (+)
unnamed: R41.1, R43.1, U5.9 (-)
unnamed: C27.2, R41.2, TP24.1, U5.8, U5.12 (+)
unnamed: R39.1, RV3.3, U5.13 (-)
unnamed: R19.2, R22.1, U6.3 (+)
unnamed: R25.1, R30.1, U6.2 (-)
unnamed: C26.2, R31.1, U6.5 (+)
unnamed: R32.1, R34.1, U6.6 (-)
unnamed: C30.2, R36.2, U6.10 (+)
unnamed: R42.1, R44.1, U6.9 (-)
unnamed: C28.2, R42.2, TP25.1, U6.8, U6.12 (+)
unnamed: R40.1, RV4.3, U6.13 (-)
PCB_TEMP_01: R74.2, TH1.2; also elsewhere on the board
PCB_TEMP_02: R75.2, TH2.2; also elsewhere on the board

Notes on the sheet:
EMG SENSOR
MOTOR ENCODERS VOLTAGE DIVIDERS
Low-pass filter
CALCULATOR
PCB TEMP SENSORS
Differential amplifier
(OpenEMG project by charleslabs.fr)
High-pass filter
Tunable amplifier

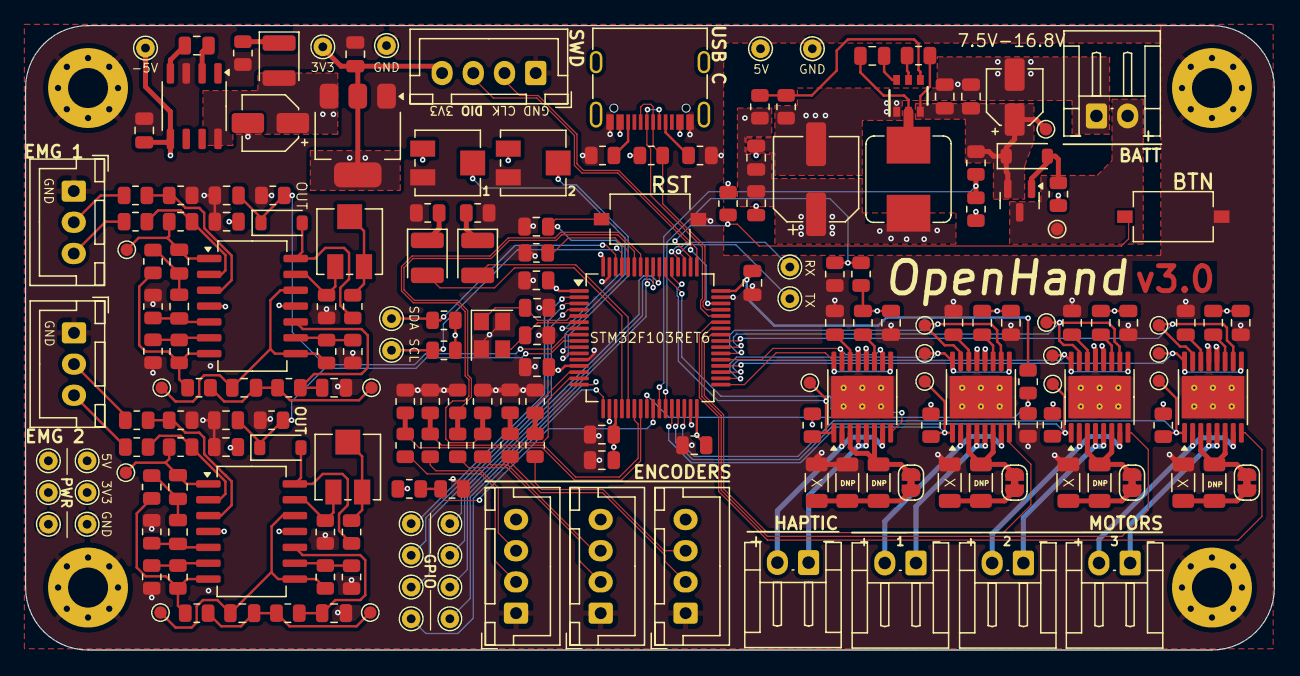
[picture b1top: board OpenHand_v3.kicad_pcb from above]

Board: 4 copper layers, 100.0 x 50.0 mm, 207 parts (0 on the bottom side), 133 nets.

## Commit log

2025-01-23 Made PCB v3, and updated CubeIDE firmware with pinout
2025-01-29 Finalize board v3, prepare CubeIDE config
2025-01-31 Update PCB via size, start with code infrastructure idea
2025-04-18 Update PCB with larger vias, add board temp sensor
